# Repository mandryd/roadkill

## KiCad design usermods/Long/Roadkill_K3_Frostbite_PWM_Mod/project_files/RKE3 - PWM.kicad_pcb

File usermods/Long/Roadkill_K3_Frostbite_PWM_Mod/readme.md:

Roadkill - K3 Frostbite PWM Mod
============
**THIS BOARD IS FOR *K3 only*.**  
***IMPORTANT*** - *Hotend fan and part cooling fan share the same (+) voltage.*
<table width=100%>
<TR><TD width=50%></TD>
       <TD width=50%></TD></TR>
<TR><TD width=50%></TD>
       <TD width=50%></TD></TR>     
<TR><TD width=50%></TD>
       <TD width=50%></TD></TR>     
</TABLE>

**Acknolwedgement:**
 - This board is 100% just a mod of roadkill.  My work pure hackery of the great work by Safflower.  Please give him all the credit he deserves.
 
 **Notes:**
 - The K3 doesn't use some of the features of the RKE2 board such as the omron probe and filament switch, so I streamlined the features somewhat.
 - This board is no longer compatible with the base roadkill.  It is only compatible with itself.
 - Changes
   - 3 pairs of wires for the heater.  RKE2 uses 2 pairs.  This adds an additional two to allow more for headroom.  
   - Part cooling fan and hotend fan share two wires for (+)
     - Partcooling fan also has two wires for (-) for the frostbite 4028 fan.
     - My 4028 fan uses 1.3 amps at full power and some 4028s use even more.
     - Adds a line for PWM on the part cooling fan (for frostbite toolhead).
     - ***IMPORTANT*** - *Hotend fan and part cooling fan share the same (+) voltage.*
   - Moved the heater screw terminal into the board a little bit.  You can use the stock side exiting wires or top exiting wires now without the terminal hanging off the side of the board.  
   - the 3 of rke3 was just a mental note for myself as to how many pairs of wires were for the heater.  I was previously using a mod with 4 pairs which i put as rke4.  This wasn't meant to confuse anyone with it being a new version of RK or something.

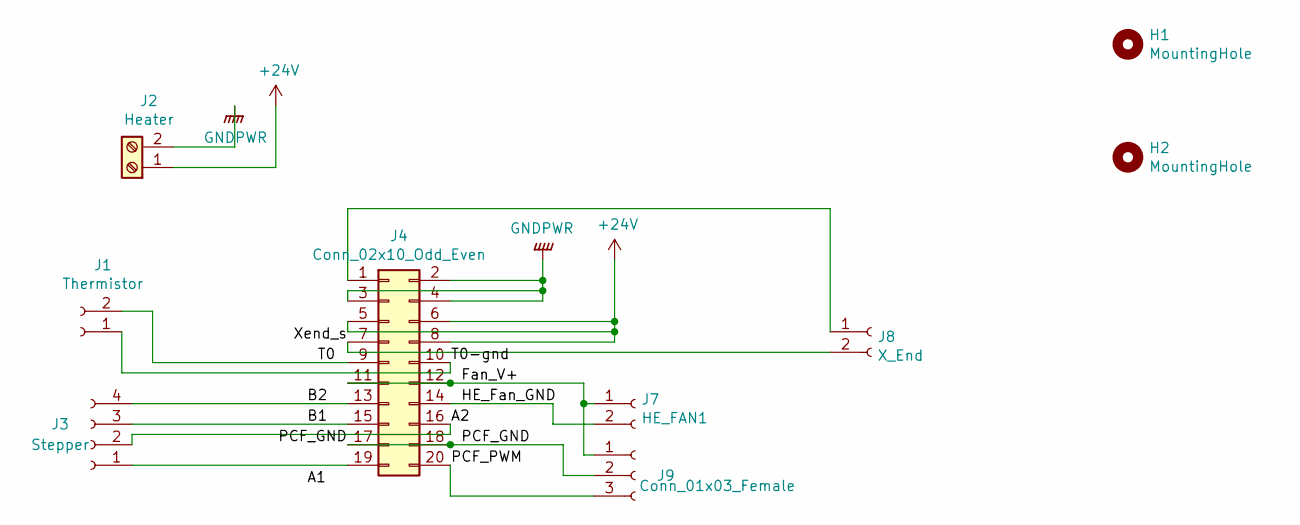
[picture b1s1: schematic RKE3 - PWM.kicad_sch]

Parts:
H1, H2: MountingHole; MountingHole_3.2mm_M3
J1: Thermistor; JST_XH_B2B-XH-A_1x02_P2.50mm_Vertical
J2: Heater; TB00250002BE
J3: Stepper; JST_XH_B4B-XH-A_1x04_P2.50mm_Vertical
J4: Conn_02x10_Odd_Even; IDC-Header_2x10_P2.54mm_Vertical
J7: HE_FAN1; JST_XH_B2B-XH-A_1x02_P2.50mm_Vertical
J8: X_End; JST_XH_B2B-XH-A_1x02_P2.50mm_Vertical
J9: Conn_01x03_Female; JST_XH_B3B-XH-A_1x03_P2.50mm_Vertical

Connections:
+24V: J2.1, J4.5, J4.6, J4.8
/A2: J3.2, J4.16
/B1: J3.3, J4.15
/B2: J3.4, J4.13
/Fan_V+: J4.11, J4.12, J7.1, J9.1
/HE_Fan_GND: J4.14, J7.2
/PCF_GND: J4.17, J4.18, J9.2
/PCF_PWM: J4.20, J9.3
/T0: J1.2, J4.9
/T0-gnd: J1.1, J4.10
/Xend_s: J4.7, J8.2
GNDPWR: J2.2, J4.2, J4.3, J4.4
unnamed: J3.1, J4.19
unnamed: J4.1, J8.1

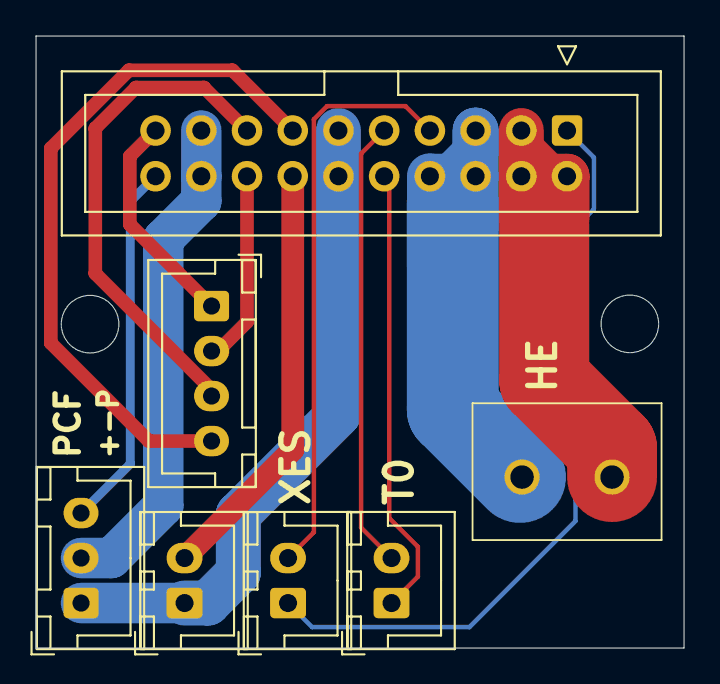
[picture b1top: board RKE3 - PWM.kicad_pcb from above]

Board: 2 copper layers, 36.0 x 34.0 mm, 9 parts (0 on the bottom side), 14 nets.

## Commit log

2022-10-14 k3 modded roadkill
2022-10-14 add some pics
2022-10-14 add pics.
2022-10-14 move files and rename directory
2022-10-14 rename files
2022-10-15 rearrange
2022-12-05 give credit where it is due.
2022-12-05 Give credit to original creator.
2023-05-26 Create Toolhead Mount - Strain Relief.stl
    added strain relief
2023-05-26 added washers

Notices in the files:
usermods/Long/Roadkill_K3_Frostbite_PWM_Mod/project_files/RKE3 - PWM.kicad_pcb:
CC BY 4.0 Safflower 2022
